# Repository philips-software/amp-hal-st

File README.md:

# amp-hal-st

**Description**:  amp-hal-st is a HAL (Hardware Abstraction Layer) implementation for a range of [ST](https://st.com) ARM Cortex-based micro-controllers. amp-hal-st implements the interfaces defined as part of [EmbeddedInfraLib].

## Dependencies

amp-hal-st requires:
- [EmbeddedInfraLib].

## How to build the software

amp-hal-st cannot be built by-itself, it must be built as part of a larger project. This paragraph describes how to add amp-hal-st to a CMake build-system, using [EmbeddedInfraLib].

> CMakeLists.txt

```cmake
cmake_minimum_required(VERSION 3.21)

project(MyProject VERSION 1.0.0)

include(FetchContent)

FetchContent_Declare(
    emil
    GIT_REPOSITORY https://github.com/philips-software/embeddedinfralib.git
    GIT_TAG        main
)

FetchContent_Declare(
    halst
    GIT_REPOSITORY https://github.com/philips-software/amp-hal-st.git
    GIT_TAG        main
)

FetchContent_MakeAvailable(emil halst)

add_executable(myprogram Main.cpp)

target_link_libraries(myprogram PUBLIC
    infra.event
    hal_st.stm32fxxx
)

halst_target_default_linker_scripts(myprogram)
halst_target_default_init(myprogram)

```

## How to test the software

Due to the nature of amp-hal-st: a HAL implementation, there are no included automated tests. Testing should be done in-context on the target hardware.

## Community

This project uses a [code-of-conduct](CODE_OF_CONDUCT.md) to define expected conduct in our community. Instances of abusive, harassing, or otherwise unacceptable behavior may be reported by contacting a project [maintainer](.github/CODEOWNERS)

## Changelog

See the [changelog](CHANGELOG.md) for more info on what's been changed.

## Contributing

Please refer to our [contributing](CONTRIBUTING.md) guide when you want to contribute to this project.

## License

amp-hal-st is licensed under the [MIT](https://choosealicense.com/licenses/mit/) [license](LICENSE) except the files and/or directories named in the [notice](NOTICE) file.

[EmbeddedInfraLib]: https://github.com/philips-software/embeddedinfralib

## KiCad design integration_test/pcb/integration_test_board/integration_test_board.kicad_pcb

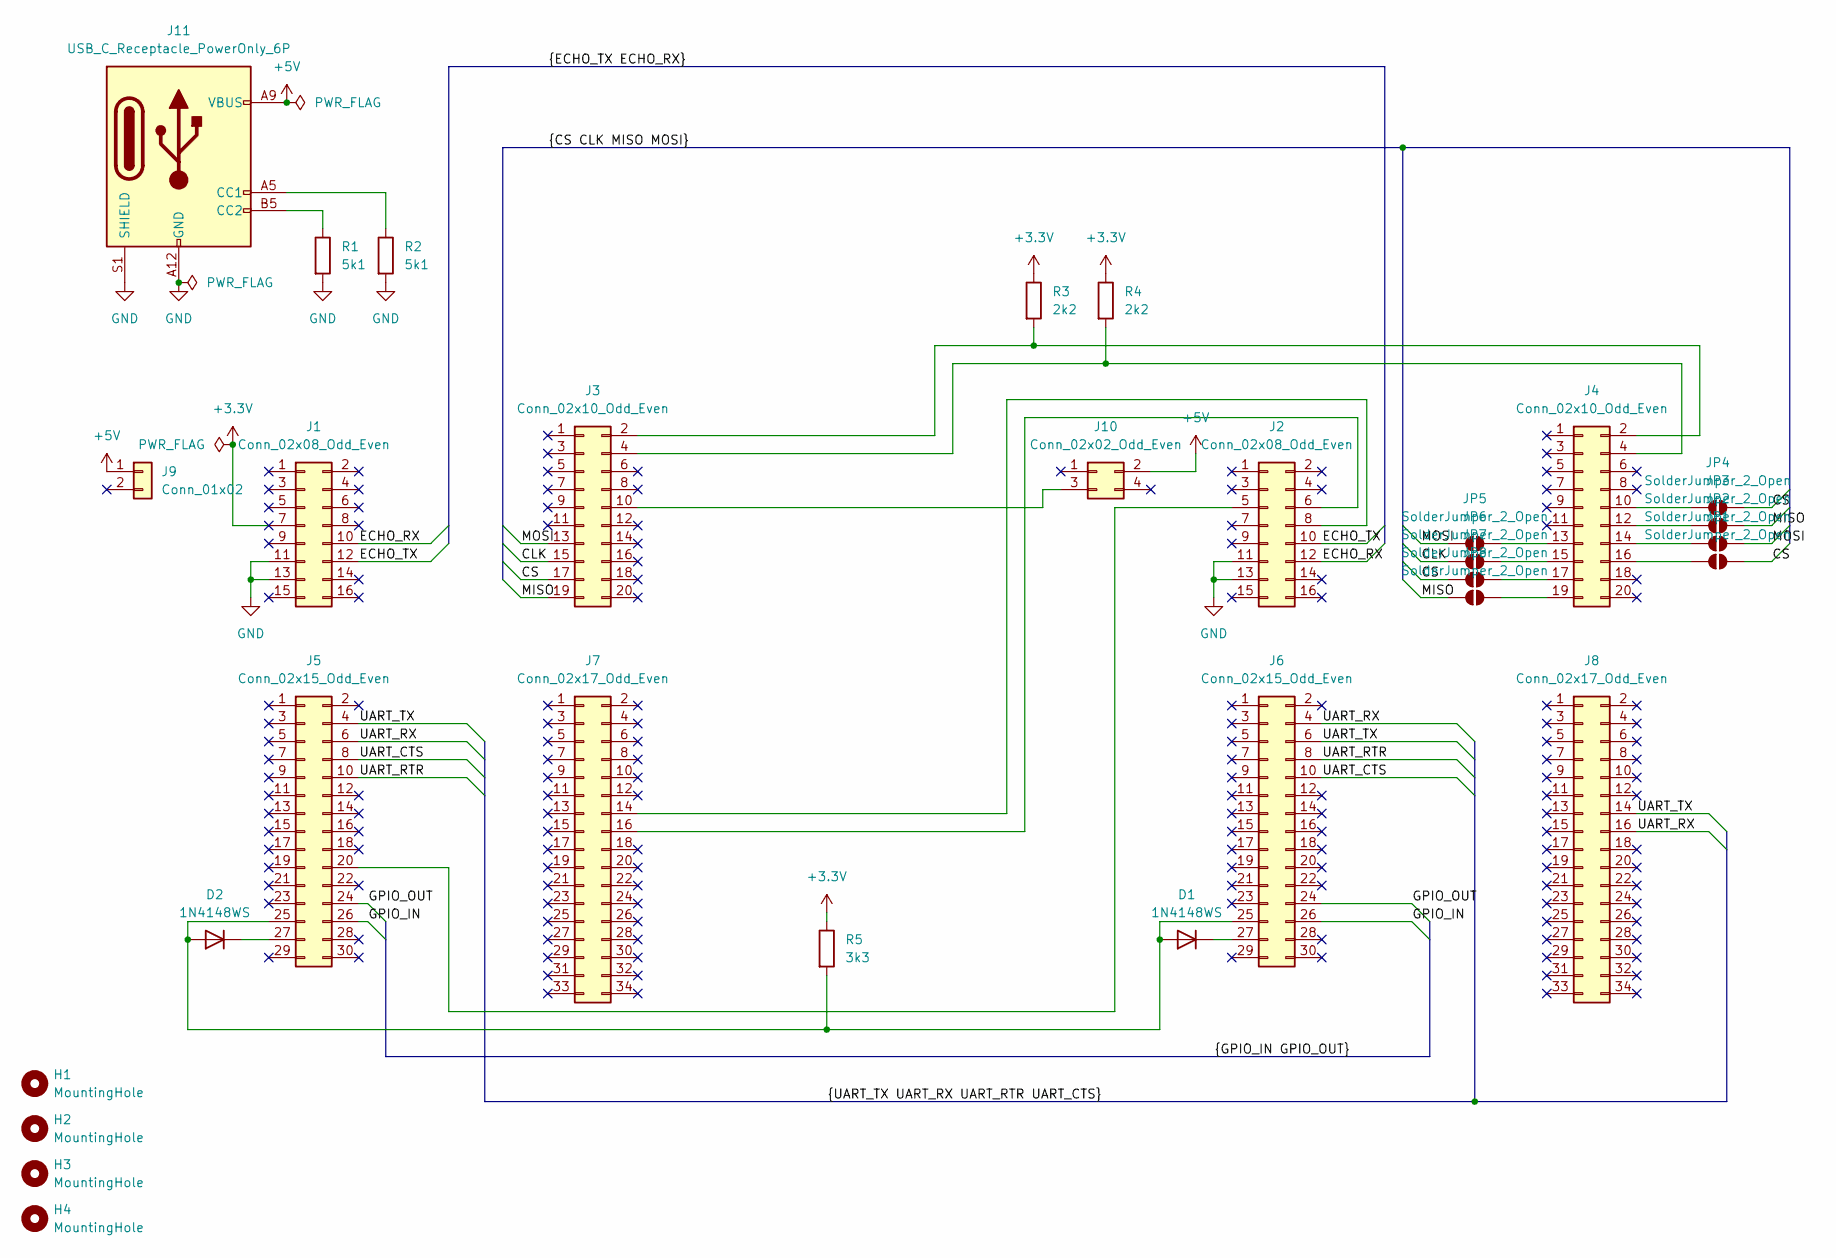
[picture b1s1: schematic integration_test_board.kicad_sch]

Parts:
D1, D2: 1N4148WS; D_SOD-323; JLCPCBPart C2128
H1, H2, H3, H4: MountingHole; MountingHole_3mm
J1, J2: Conn_02x08_Odd_Even; PinHeader_2x08_P2.54mm_Vertical; JLCPCBPart C42385715
J3, J4: Conn_02x10_Odd_Even; PinHeader_2x10_P2.54mm_Vertical; JLCPCBPart C2685085
J5, J6: Conn_02x15_Odd_Even; PinHeader_2x15_P2.54mm_Vertical; JLCPCBPart C25503127
J7, J8: Conn_02x17_Odd_Even; PinHeader_2x17_P2.54mm_Vertical; JLCPCBPart C5371994
J9: Conn_01x02; PinSocket_1x02_P2.54mm_Vertical; JLCPCBPart C7509512
J10: Conn_02x02_Odd_Even; PinHeader_2x02_P2.54mm_Vertical; JLCPCBPart C47553
J11: USB_C_Receptacle_PowerOnly_6P; USB_C_Receptacle_GCT_USB4125-xx-x-0190_6P_TopMnt_Horizontal; JLCPCBPart C5246813
JP1, JP2, JP3, JP4, JP5, JP6, JP7, JP8: SolderJumper_2_Open; SolderJumper-2_P1.3mm_Open_TrianglePad1.0x1.5mm
R1, R2: 5k1; R_0603_1608Metric; JLCPCBPart C23186
R3, R4: 2k2; R_0603_1608Metric; JLCPCBPart C4190
R5: 3k3; R_0603_1608Metric; JLCPCBPart C22978

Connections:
+3.3V: J1.7, R3.1, R4.1, R5.1
+5V: J9.1, J10.2, J11.A9 (VBUS), J11.B9 (VBUS)
/CLK: J3.15, JP6.1 (A)
/CS: J3.17, JP1.2 (B), JP4.2 (B), JP7.1 (A)
/ECHO_RX: J1.10, J2.12
/ECHO_TX: J1.12, J2.10
/GPIO_IN: J5.26, J6.26
/GPIO_OUT: J5.24, J6.24
/MISO: J3.19, JP3.2 (B), JP8.1 (A)
/MOSI: J3.13, JP2.2 (B), JP5.1 (A)
/UART_CTS: J5.8, J6.10
/UART_RTR: J5.10, J6.8
/UART_RX: J5.6, J6.4, J8.16
/UART_TX: J5.4, J6.6, J8.14
GND: J1.11, J1.13, J2.11, J2.13, J11.A12 (GND), J11.B12 (GND), J11.S1 (SHIELD), R1.2, R2.2
unnamed: D1.2 (A), D2.2 (A), J5.25, J6.25, R5.2
unnamed: D1.1 (K), J6.27
unnamed: D2.1 (K), J5.27
unnamed: J2.5, J5.20
unnamed: J2.6, J7.16
unnamed: J2.8, J7.14
unnamed: J3.2, J4.2, R3.2
unnamed: J3.4, J4.4, R4.2
unnamed: J4.10, JP4.1 (A)
unnamed: J4.12, JP3.1 (A)
unnamed: J4.13, JP5.2 (B)
unnamed: J4.14, JP2.1 (A)
unnamed: J4.15, JP6.2 (B)
unnamed: J4.16, JP1.1 (A)
unnamed: J4.17, JP7.2 (B)
unnamed: J4.19, JP8.2 (B)
unnamed: J3.10, J10.3
unnamed: J11.A5 (CC1), R2.1
unnamed: J11.B5 (CC2), R1.1

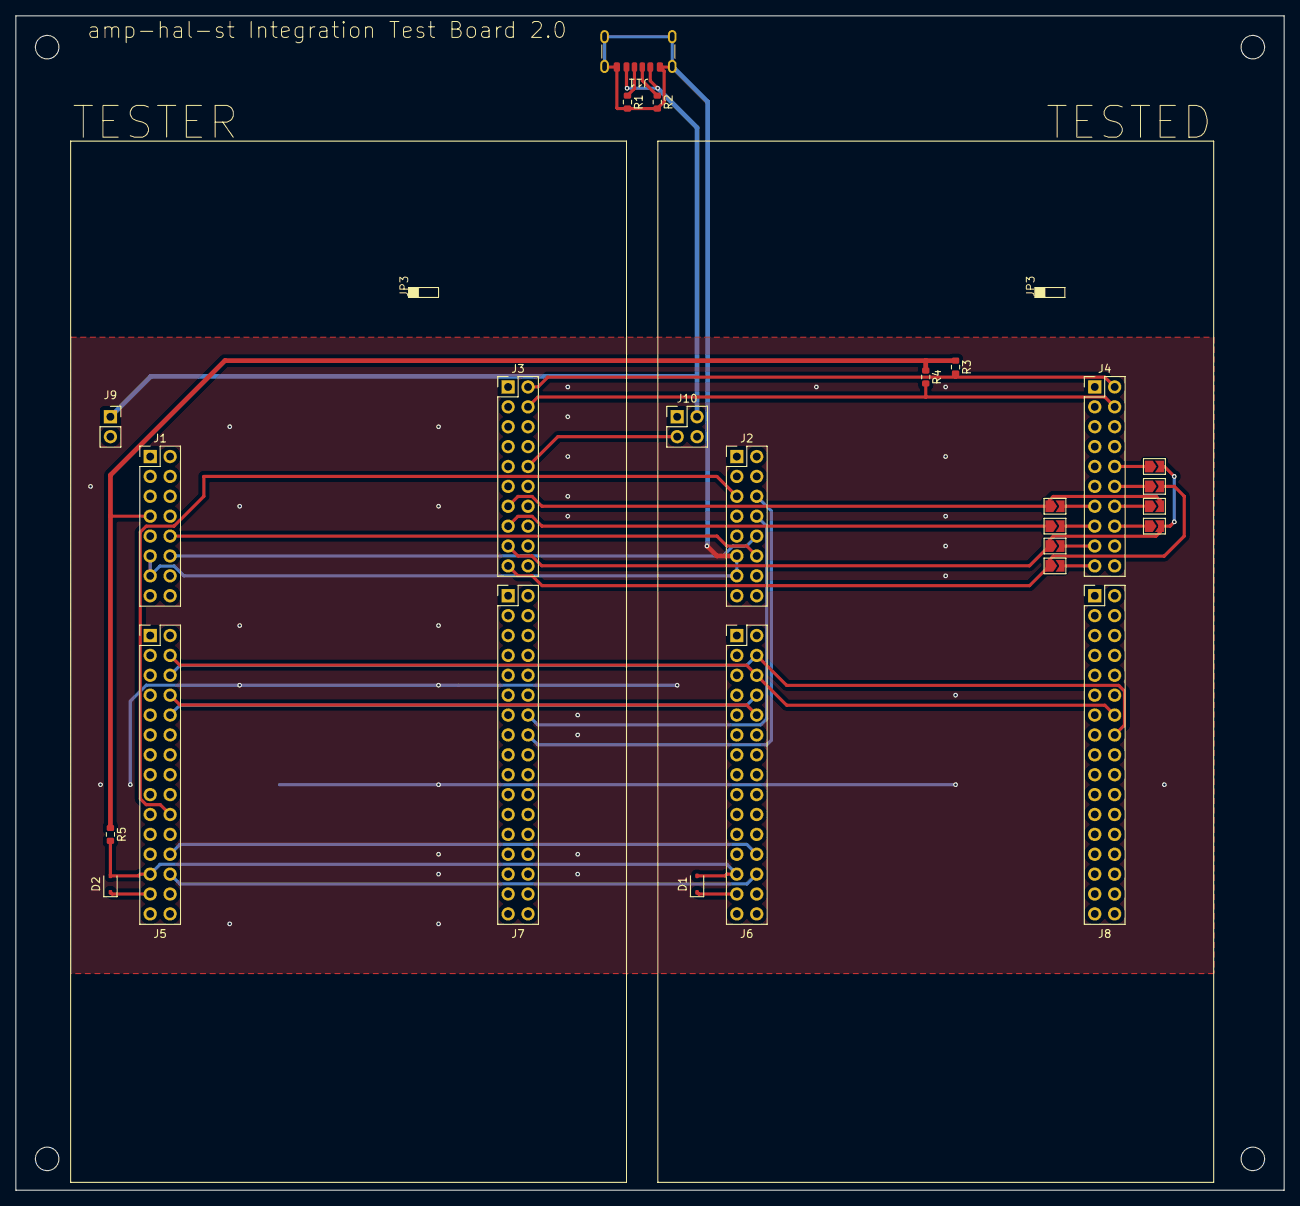
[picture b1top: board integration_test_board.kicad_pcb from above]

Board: 2 copper layers, 162.0 x 150.0 mm, 30 parts (0 on the bottom side), 34 nets.

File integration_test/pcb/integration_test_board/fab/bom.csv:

"Value","Reference","Footprint","JLCPCBPart"
"1N4148WS","D1,D2","Diode_SMD:D_SOD-323","C2128"
"Conn_02x08_Odd_Even","J1,J2","Connector_PinHeader_2.54mm:PinHeader_2x08_P2.54mm_Vertical","C42385715"
"Conn_02x10_Odd_Even","J3,J4","Connector_PinHeader_2.54mm:PinHeader_2x10_P2.54mm_Vertical","C2685085"
"Conn_02x15_Odd_Even","J5,J6","Connector_PinHeader_2.54mm:PinHeader_2x15_P2.54mm_Vertical","C25503127"
"Conn_02x17_Odd_Even","J7,J8","Connector_PinHeader_2.54mm:PinHeader_2x17_P2.54mm_Vertical","C5371994"
"Conn_01x02","J9","Connector_PinSocket_2.54mm:PinSocket_1x02_P2.54mm_Vertical","C7509512"
"Conn_02x02_Odd_Even","J10","Connector_PinHeader_2.54mm:PinHeader_2x02_P2.54mm_Vertical","C47553"
"USB_C_Receptacle_PowerOnly_6P","J11","Connector_USB:USB_C_Receptacle_GCT_USB4125-xx-x-0190_6P_TopMnt_Horizontal","C5246813"
"5k1","R1,R2","Resistor_SMD:R_0603_1608Metric","C23186"
"2k2","R3,R4","Resistor_SMD:R_0603_1608Metric","C4190"
"3k3","R5","Resistor_SMD:R_0603_1608Metric","C22978"

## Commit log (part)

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2026-05-29 chore: add set privacy mode to gap central implementation (#815)
    * add set privacy mode to gap central impl
    * update emil hash
    * refactored gap init
    * make sure the device is in standby before to perform a ble stack reset
    * update set address
    * update emil hash
2026-06-01 build(deps): bump philips-software/amp-devcontainer-cpp
    Bumps [philips-software/amp-devcontainer-cpp](https://github.com/philips-software/amp-devcontainer) from 6.10.3 to 7.0.0.
    - [Release notes](https://github.com/philips-software/amp-devcontainer/releases)
    - [Changelog](https://github.com/philips-software/amp-devcontainer/blob/main/CHANGELOG.md)
    - [Commits](https://github.com/philips-software/amp-devcontainer/compare/v6.10.3...v7.0.0)
    ---
    updated-dependencies:
2026-06-01 build: use correct hash from amp-embedded-infra-lib
2026-06-01 build: use correct hash from amp-embedded-infra-lib (#819)
2026-06-01 build(ci): update workflow devcontainer image to v7.0.0
2026-06-02 update WBA wireless stack
2026-06-03 build(deps): bump philips-software/amp-devcontainer-cpp
    Bumps [philips-software/amp-devcontainer-cpp](https://github.com/philips-software/amp-devcontainer) from 7.0.0 to 7.2.0.
    - [Release notes](https://github.com/philips-software/amp-devcontainer/releases)
    - [Changelog](https://github.com/philips-software/amp-devcontainer/blob/main/CHANGELOG.md)
    - [Commits](https://github.com/philips-software/amp-devcontainer/compare/v7.0.0...v7.2.0)
    ---
    updated-dependencies:
2026-06-08 chore: update amp-embedded-infra-lib hash to 948e98d955d2e70b1d74ba63d53f953f7b7b051a
2026-06-08 Consolidate pairing succeeded and failed
2026-06-08 Fix DiscoveredDevice
2026-06-08 Remove StopDeviceDiscovery
2026-06-08 REname Disconnect to Standby
2026-06-08 Remove CancelConnect
2026-06-09 build(deps): bump the github-actions group with 2 updates
    Bumps the github-actions group with 2 updates: [actions/checkout](https://github.com/actions/checkout) and [github/codeql-action](https://github.com/github/codeql-action).
    Updates `actions/checkout` from 6.0.2 to 6.0.3
    - [Release notes](https://github.com/actions/checkout/releases)
    - [Changelog](https://github.com/actions/checkout/blob/main/CHANGELOG.md)
    - [Commits](https://github.com/actions/checkout/compare/de0fac2e4500dabe0009e67214ff5f5447ce83dd...df4cb1c069e1874edd31b4311f1884172cec0e10)
    Updates `github/codeql-action` from 4.36.0 to 4.36.1
2026-06-09 DisplayPasskey -> AuthenticationRequired
2026-06-09 build(deps): bump the github-actions group with 2 updates (#823)
    Bumps the github-actions group with 2 updates: [actions/checkout](https://github.com/actions/checkout) and [github/codeql-action](https://github.com/github/codeql-action).
    Updates `actions/checkout` from 6.0.2 to 6.0.3
    - [Release notes](https://github.com/actions/checkout/releases)
    - [Changelog](https://github.com/actions/checkout/blob/main/CHANGELOG.md)
    - [Commits](https://github.com/actions/checkout/compare/de0fac2e4500dabe0009e67214ff5f5447ce83dd...df4cb1c069e1874edd31b4311f1884172cec0e10)
    Updates `github/codeql-action` from 4.36.0 to 4.36.1
2026-06-09 ci: align workflow devcontainer image version to 7.2.0
2026-06-09 ci: suppress clang-22 mbedtls warnings for clang-cl Windows cross-compilation
2026-06-09 fix: suppress clang-22 mbedtls warnings using cmake 4.x compatible approach
    The previous fix used CMAKE_C_SIMULATE_ID STREQUAL "MSVC" before project() which
    doesn't reliably detect clang-cl in cmake 4.x. Additionally, Emil's generator
    expression $<CXX_COMPILER_ID:Clang> does not evaluate to true for C-language targets.
    Changes:
    - CMakeLists.txt: move mbedtls warning suppression after project(), use
    CMAKE_C_COMPILER_FRONTEND_VARIANT (reliable in cmake 4.x for clang-cl detection)
2026-06-09 fix: remove unreliable CMAKE_C_SIMULATE_ID fallback from condition
    Use only CMAKE_C_COMPILER_FRONTEND_VARIANT STREQUAL "MSVC" to detect clang-cl,
    since CMAKE_C_SIMULATE_ID is not reliably set in cmake 4.x for standalone clang-cl.
    CMAKE_C_COMPILER_FRONTEND_VARIANT is available since cmake 3.14 which is well below
    our minimum required version of 3.24.
2026-06-09 ST builds
2026-06-09 Slightly expand pairing failed reason
2026-06-10 Implement RemoveBondWithAddress
2026-06-11 build(deps): bump github/codeql-action in the github-actions group
    Bumps the github-actions group with 1 update: [github/codeql-action](https://github.com/github/codeql-action).
    Updates `github/codeql-action` from 4.36.1 to 4.36.2
    - [Release notes](https://github.com/github/codeql-action/releases)
    - [Changelog](https://github.com/github/codeql-action/blob/main/CHANGELOG.md)
    - [Commits](https://github.com/github/codeql-action/compare/87557b9c84dde89fdd9b10e88954ac2f4248e463...8aad20d150bbac5944a9f9d289da16a4b0d87c1e)
    ---
2026-06-11 build(deps): bump github/codeql-action from 4.36.1 to 4.36.2 in the github-actions group (#825)
    build(deps): bump github/codeql-action in the github-actions group
    Bumps the github-actions group with 1 update: [github/codeql-action](https://github.com/github/codeql-action).
    Updates `github/codeql-action` from 4.36.1 to 4.36.2
    - [Release notes](https://github.com/github/codeql-action/releases)
    - [Changelog](https://github.com/github/codeql-action/blob/main/CHANGELOG.md)
    - [Commits](https://github.com/github/codeql-action/compare/87557b9c84dde89fdd9b10e88954ac2f4248e463...8aad20d150bbac5944a9f9d289da16a4b0d87c1e)
2026-06-11 chore(main): release 4.1.0
2026-06-11 chore: update amp-embedded-infra-lib hash to 948e98d955d2e70b1d74ba63d53f953f7b7b051a (#821)
2026-06-11 try fix build
2026-06-11 Set filterDuplicatesEnabled = 0
2026-06-11 Implement bondlist stubs
2026-06-11 Bump EMIL hash
2026-06-15 chore: update amp-embedded-infra-lib hash to 555510ac8c5036b7288a6cbf79bc40e5c8f3afdd
2026-06-15 Apply suggestion from @andjordan
2026-06-15 Fix copilot comments
2026-06-15 Remove maximumAllowedBonds from BondList
2026-06-16 chore: update amp-embedded-infra-lib hash to 555510ac8c5036b7288a6cbf79bc40e5c8f3afdd (#827)
2026-06-16 fix: set CCR_FETCH_DEPS ON to fix CLI11 not found in Windows host build
2026-06-16 Update EMIL hash
2026-06-16 feat!: improve GapCentral Echo interface (#822)
    * Consolidate pairing succeeded and failed
    * Fix DiscoveredDevice
    * Remove StopDeviceDiscovery
    * REname Disconnect to Standby
    * Remove CancelConnect
    * DisplayPasskey -> AuthenticationRequired
2026-06-17 chore: remove redundent publish of Standby state
2026-06-18 feat: disable filterDuplicatesEnabled in GapCentralSt (#826)
    Set filterDuplicatesEnabled = 0
2026-06-18 chore: remove notifying observers of standby state (#828)
    chore: remove redundent publish of Standby state
2026-06-22 chore: update amp-embedded-infra-lib hash to 8ae868c769e044567e886bb247a84cc96e4e0f32
2026-06-23 Update interface
2026-06-24 build(deps): bump actions/checkout from 6.0.3 to 7.0.0
    Bumps [actions/checkout](https://github.com/actions/checkout) from 6.0.3 to 7.0.0.
    - [Release notes](https://github.com/actions/checkout/releases)
    - [Changelog](https://github.com/actions/checkout/blob/main/CHANGELOG.md)
    - [Commits](https://github.com/actions/checkout/compare/df4cb1c069e1874edd31b4311f1884172cec0e10...9c091bb21b7c1c1d1991bb908d89e4e9dddfe3e0)
    ---
    updated-dependencies:
2026-06-24 build(deps): bump actions/checkout from 6.0.3 to 7.0.0 (#831)
    Bumps [actions/checkout](https://github.com/actions/checkout) from 6.0.3 to 7.0.0.
    - [Release notes](https://github.com/actions/checkout/releases)
    - [Changelog](https://github.com/actions/checkout/blob/main/CHANGELOG.md)
    - [Commits](https://github.com/actions/checkout/compare/df4cb1c069e1874edd31b4311f1884172cec0e10...9c091bb21b7c1c1d1991bb908d89e4e9dddfe3e0)
    ---
    updated-dependencies:
2026-06-25 feat: make WatchDogStm config initializable as aggregate
2026-06-25 feat: make WatchDogStm config initializable as aggregate (#832)
2026-06-25 feat: implement bond aging update for connected peers in GapSt
2026-06-25 fix: correct address type handling in UpdateBondAgingForConnectedPeer
2026-06-25 Update CMakeLists
2026-06-29 chore: update amp-embedded-infra-lib hash to 256685e343454add2e57e3b86db0669a8b08c491
2026-06-29 Update hash
2026-06-30 build(deps): bump reviewdog/action-suggester
    Bumps the github-actions group with 1 update in the / directory: [reviewdog/action-suggester](https://github.com/reviewdog/action-suggester).
    Updates `reviewdog/action-suggester` from 1.24.0 to 1.24.3
    - [Release notes](https://github.com/reviewdog/action-suggester/releases)
    - [Commits](https://github.com/reviewdog/action-suggester/compare/aa38384ceb608d00f84b4690cacc83a5aba307ff...2558ba17e65a9039e73764a73009fc05fef28a46)
    ---
    updated-dependencies:
2026-06-30 build(deps): bump reviewdog/action-suggester from 1.24.0 to 1.24.3 in the github-actions group across 1 directory (#834)
    build(deps): bump reviewdog/action-suggester
    Bumps the github-actions group with 1 update in the / directory: [reviewdog/action-suggester](https://github.com/reviewdog/action-suggester).
    Updates `reviewdog/action-suggester` from 1.24.0 to 1.24.3
    - [Release notes](https://github.com/reviewdog/action-suggester/releases)
    - [Commits](https://github.com/reviewdog/action-suggester/compare/aa38384ceb608d00f84b4690cacc83a5aba307ff...2558ba17e65a9039e73764a73009fc05fef28a46)
    ---
2026-06-30 chore(main): release 5.0.0
